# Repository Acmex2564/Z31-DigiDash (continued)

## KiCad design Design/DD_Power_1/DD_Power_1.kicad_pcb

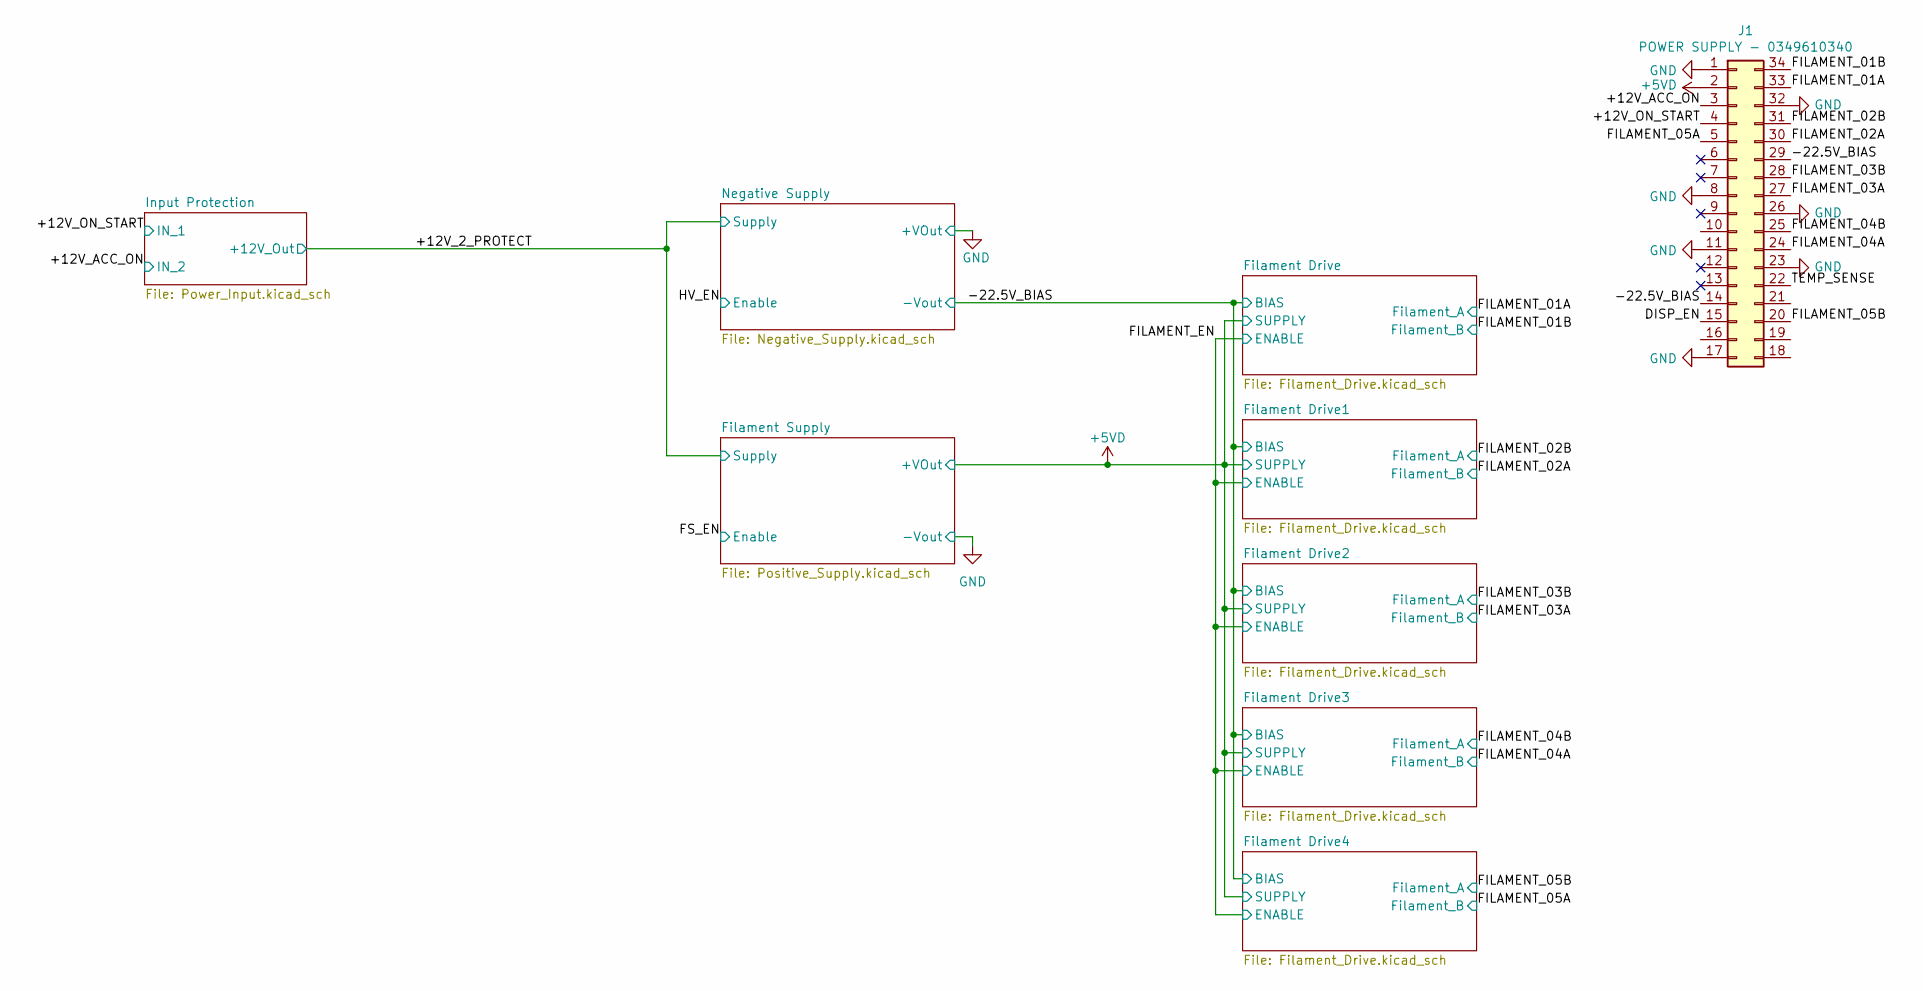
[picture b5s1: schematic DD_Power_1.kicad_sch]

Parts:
J1: POWER SUPPLY - 0349610340; 34961

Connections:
+5VD: J1.2; also elsewhere on the board
/+12V_ACC_ON: J1.3; also elsewhere on the board
/+12V_CONST: J1.21
/+12V_ON_START: J1.4; also elsewhere on the board
/-22.5V_BIAS: J1.14, J1.29; also elsewhere on the board
/DISP_EN: J1.15
/FILAMENT_01A: J1.33; also elsewhere on the board
/FILAMENT_01B: J1.34; also elsewhere on the board
/FILAMENT_02A: J1.30; also elsewhere on the board
/FILAMENT_02B: J1.31; also elsewhere on the board
/FILAMENT_03A: J1.27; also elsewhere on the board
/FILAMENT_03B: J1.28; also elsewhere on the board
/FILAMENT_04A: J1.24; also elsewhere on the board
/FILAMENT_04B: J1.25; also elsewhere on the board
/FILAMENT_05A: J1.5; also elsewhere on the board
/FILAMENT_05B: J1.20; also elsewhere on the board
/TEMP_SENSE: J1.22
GND: J1.1, J1.8, J1.11, J1.17, J1.23, J1.26, J1.32; also elsewhere on the board

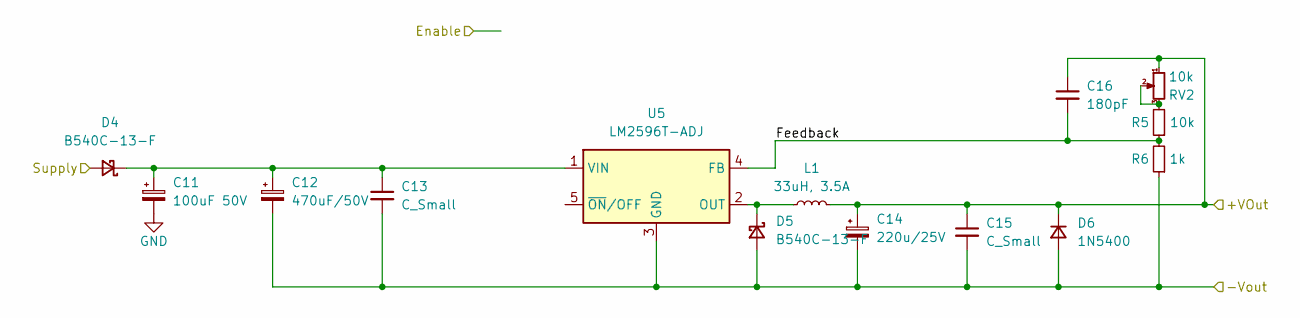
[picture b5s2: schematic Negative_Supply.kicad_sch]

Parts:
C11: 100uF 50V; CP_Radial_D8.0mm_P3.50mm
C12: 470uF/50V; CP_Radial_D12.5mm_P5.00mm
C13, C15: C_Small; C_0805_2012Metric_Pad1.18x1.45mm_HandSolder
C14: 220u/25V; CP_Radial_D6.3mm_P2.50mm
C16: 180pF; C_0805_2012Metric_Pad1.18x1.45mm_HandSolder
D4, D5: B540C-13-F; D_SMC
D6: 1N5400; D_SMC
L1: 33uH, 3.5A; L_Bourns_SRR1260
R5: 10k; R_0805_2012Metric_Pad1.20x1.40mm_HandSolder
R6: 1k; R_0805_2012Metric_Pad1.20x1.40mm_HandSolder
RV2: 10k; Potentiometer_Vishay_TS53YJ_Vertical
U5: LM2596T-ADJ; TO-220-5_P3.4x3.7mm_StaggerOdd_Lead3.8mm_Vertical

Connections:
/+12V_2_PROTECT: D4.2 (A); also elsewhere on the board
/-22.5V_BIAS: C12.2, C13.2, C14.2, C15.2, D5.2 (A), D6.2 (A), R6.1, U5.3 (GND); also elsewhere on the board
/Negative Supply/Feedback: C16.2, R5.1, R6.2, U5.4 (FB)
GND: C11.2, C14.1, C15.1, C16.1, D6.1 (K), L1.2, RV2.1; also elsewhere on the board
unnamed: C11.1, C12.1, C13.1, D4.1 (K), U5.1 (VIN)
unnamed: D5.1 (K), L1.1, U5.2 (OUT)
unnamed: R5.2, RV2.2, RV2.3

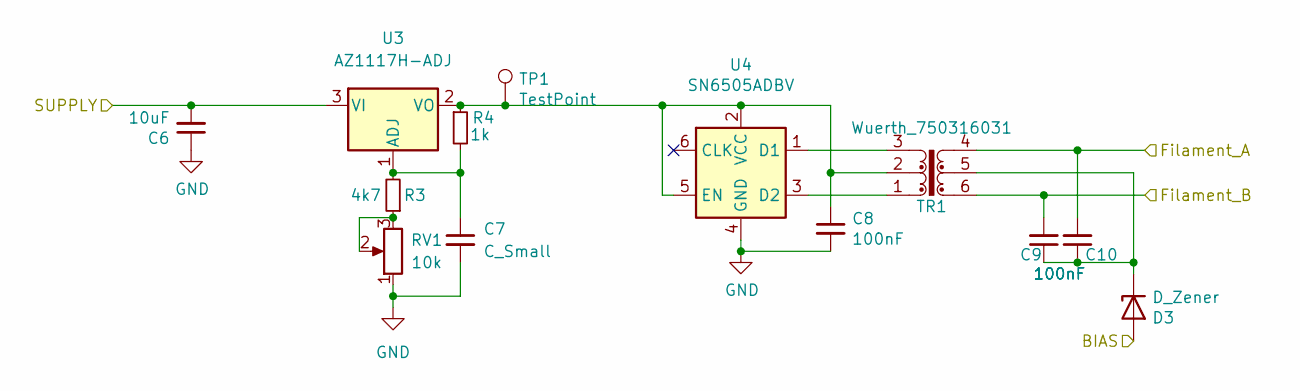
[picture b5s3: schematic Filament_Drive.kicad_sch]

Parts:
C6: 10uF; C_1206_3216Metric_Pad1.33x1.80mm_HandSolder
C7: C_Small; C_0805_2012Metric_Pad1.18x1.45mm_HandSolder
C8, C9, C10: 100nF; C_0805_2012Metric_Pad1.18x1.45mm_HandSolder
D3: D_Zener; D_SOD-123
R3: 4k7; R_0805_2012Metric_Pad1.20x1.40mm_HandSolder
R4: 1k; R_0805_2012Metric_Pad1.20x1.40mm_HandSolder
RV1: 10k; Potentiometer_Vishay_TS53YL_Vertical
TP1: TestPoint; TestPoint_2Pads_Pitch2.54mm_Drill0.8mm
TR1: Wuerth_750316031; Transformer_Wuerth_750315371
U3: AZ1117H-ADJ; SOT-223-3_TabPin2
U4: SN6505ADBV; SOT-23-6

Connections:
+5VD: C6.2, U3.3 (VI); also elsewhere on the board
/-22.5V_BIAS: D3.2 (A); also elsewhere on the board
/FILAMENT_01A: C10.2, TR1.4; also elsewhere on the board
/FILAMENT_01B: C9.2, TR1.6; also elsewhere on the board
GND: C6.1, C7.2, C8.2, RV1.1, U4.4 (GND); also elsewhere on the board
unnamed: C7.1, R3.2, R4.2, U3.1 (ADJ)
unnamed: C8.1, R4.1, TP1.1, TR1.2, U3.2 (VO), U4.2 (VCC), U4.5 (EN)
unnamed: C9.1, C10.1, D3.1 (K), TR1.5
unnamed: R3.1, RV1.2, RV1.3
unnamed: TR1.1, U4.3 (D2)
unnamed: TR1.3, U4.1 (D1)

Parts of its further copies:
C21, C26, C31, C36: 10uF; C_1206_3216Metric_Pad1.33x1.80mm_HandSolder
C22, C27, C32, C37: C_Small; C_0805_2012Metric_Pad1.18x1.45mm_HandSolder
C23, C24, C25, C28, C29, C30, C33, C34, C35, C38, C39, C40: 100nF; C_0805_2012Metric_Pad1.18x1.45mm_HandSolder
D8, D9, D10, D11: D_Zener; D_SOD-123
R7, R9, R11, R13: 4k7; R_0805_2012Metric_Pad1.20x1.40mm_HandSolder
R8, R10, R12, R14: 1k; R_0805_2012Metric_Pad1.20x1.40mm_HandSolder
RV3, RV4, RV5, RV6: 10k; Potentiometer_Vishay_TS53YL_Vertical
TP2, TP3, TP4, TP5: TestPoint; TestPoint_2Pads_Pitch2.54mm_Drill0.8mm
TR2, TR3, TR4, TR5: Wuerth_750316031; Transformer_Wuerth_750315371
U7, U9, U11, U13: AZ1117H-ADJ; SOT-223-3_TabPin2
U8, U10, U12, U14: SN6505ADBV; SOT-23-6

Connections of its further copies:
+5VD: C21.2, C26.2, C31.2, C36.2, U7.3 (VI), U9.3 (VI), U11.3 (VI), U13.3 (VI); also elsewhere on the board
/-22.5V_BIAS: D8.2 (A), D9.2 (A), D10.2 (A), D11.2 (A); also elsewhere on the board
/FILAMENT_02A: C24.2, TR2.6; also elsewhere on the board
/FILAMENT_02B: C25.2, TR2.4; also elsewhere on the board
/FILAMENT_03A: C29.2, TR3.6; also elsewhere on the board
/FILAMENT_03B: C30.2, TR3.4; also elsewhere on the board
/FILAMENT_04A: C34.2, TR4.6; also elsewhere on the board
/FILAMENT_04B: C35.2, TR4.4; also elsewhere on the board
/FILAMENT_05A: C39.2, TR5.6; also elsewhere on the board
/FILAMENT_05B: C40.2, TR5.4; also elsewhere on the board
GND: C21.1, C22.2, C23.2, C26.1, C27.2, C28.2, C31.1, C32.2, C33.2, C36.1, C37.2, C38.2, RV3.1, RV4.1, RV5.1, RV6.1, U8.4 (GND), U10.4 (GND), U12.4 (GND), U14.4 (GND); also elsewhere on the board
unnamed: C22.1, R7.2, R8.2, U7.1 (ADJ)
unnamed: C23.1, R8.1, TP2.1, TR2.2, U7.2 (VO), U8.2 (VCC), U8.5 (EN)
unnamed: C24.1, C25.1, D8.1 (K), TR2.5
unnamed: C27.1, R9.2, R10.2, U9.1 (ADJ)
unnamed: C28.1, R10.1, TP3.1, TR3.2, U9.2 (VO), U10.2 (VCC), U10.5 (EN)
unnamed: C29.1, C30.1, D9.1 (K), TR3.5
unnamed: C32.1, R11.2, R12.2, U11.1 (ADJ)
unnamed: C33.1, R12.1, TP4.1, TR4.2, U11.2 (VO), U12.2 (VCC), U12.5 (EN)
unnamed: C34.1, C35.1, D10.1 (K), TR4.5
unnamed: C37.1, R13.2, R14.2, U13.1 (ADJ)
unnamed: C38.1, R14.1, TP5.1, TR5.2, U13.2 (VO), U14.2 (VCC), U14.5 (EN)
unnamed: C39.1, C40.1, D11.1 (K), TR5.5
unnamed: R7.1, RV3.2, RV3.3
unnamed: R9.1, RV4.2, RV4.3
unnamed: R11.1, RV5.2, RV5.3
unnamed: R13.1, RV6.2, RV6.3
unnamed: TR2.1, U8.3 (D2)
unnamed: TR2.3, U8.1 (D1)
unnamed: TR3.1, U10.3 (D2)
unnamed: TR3.3, U10.1 (D1)
unnamed: TR4.1, U12.3 (D2)
unnamed: TR4.3, U12.1 (D1)
unnamed: TR5.1, U14.3 (D2)
unnamed: TR5.3, U14.1 (D1)

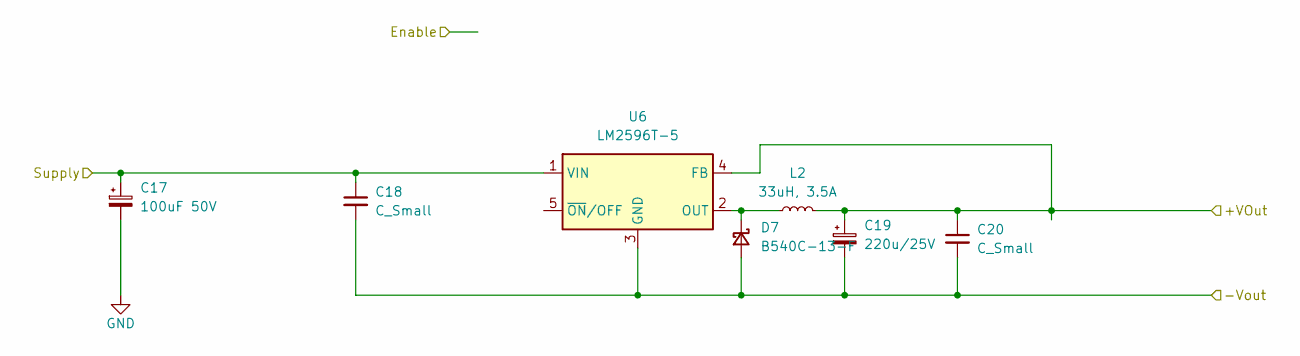
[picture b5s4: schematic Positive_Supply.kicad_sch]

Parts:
C17: 100uF 50V; CP_Radial_D8.0mm_P3.50mm
C18, C20: C_Small; C_0805_2012Metric_Pad1.18x1.45mm_HandSolder
C19: 220u/25V; CP_Radial_D6.3mm_P2.50mm
D7: B540C-13-F; D_SMC
L2: 33uH, 3.5A; L_Bourns_SRR1260
U6: LM2596T-5; TO-220-5_P3.4x3.7mm_StaggerOdd_Lead3.8mm_Vertical

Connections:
+5VD: C19.1, C20.1, L2.2, U6.4 (FB); also elsewhere on the board
/+12V_2_PROTECT: C17.1, C18.1, U6.1 (VIN); also elsewhere on the board
GND: C17.2, C18.2, C19.2, C20.2, D7.2 (A), U6.3 (GND); also elsewhere on the board
unnamed: D7.1 (K), L2.1, U6.2 (OUT)

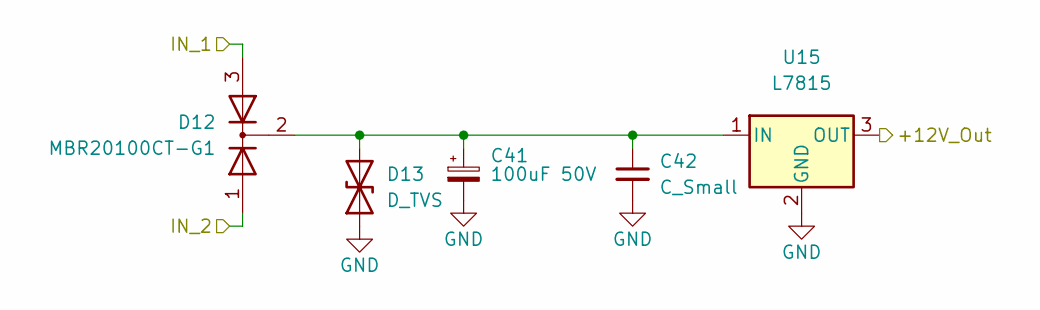
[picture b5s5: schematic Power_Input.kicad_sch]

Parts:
C41: 100uF 50V; CP_Radial_D8.0mm_P3.50mm
C42: C_Small
D12: MBR20100CT-G1; TO-220-3_Vertical
D13: D_TVS; D_SMC
U15: L7815; TO-220-3_Vertical

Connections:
/+12V_2_PROTECT: U15.3 (OUT); also elsewhere on the board
/+12V_ACC_ON: D12.1 (A); also elsewhere on the board
/+12V_ON_START: D12.3 (A); also elsewhere on the board
GND: C41.2, C42.2, D13.1 (A1), U15.2 (GND); also elsewhere on the board
unnamed: C41.1, C42.1, D12.2 (K), D13.2 (A2), U15.1 (IN)

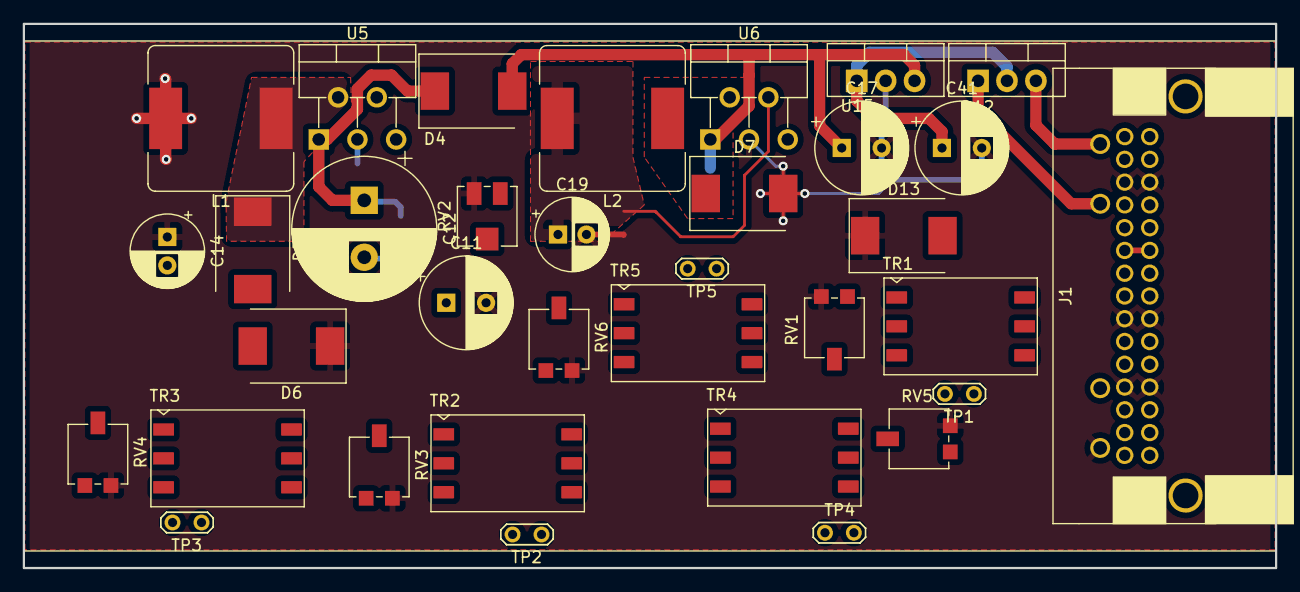
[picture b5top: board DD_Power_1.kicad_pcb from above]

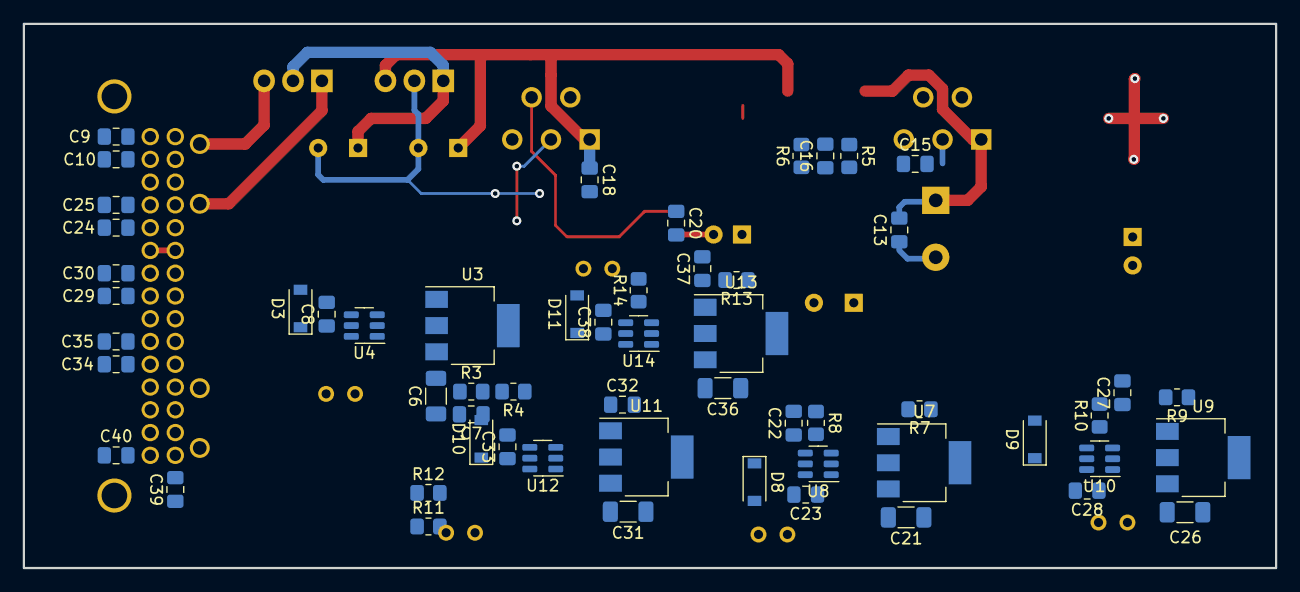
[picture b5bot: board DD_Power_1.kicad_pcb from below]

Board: 4 copper layers, 110.0 x 47.8 mm, 91 parts (57 on the bottom side), 52 nets.

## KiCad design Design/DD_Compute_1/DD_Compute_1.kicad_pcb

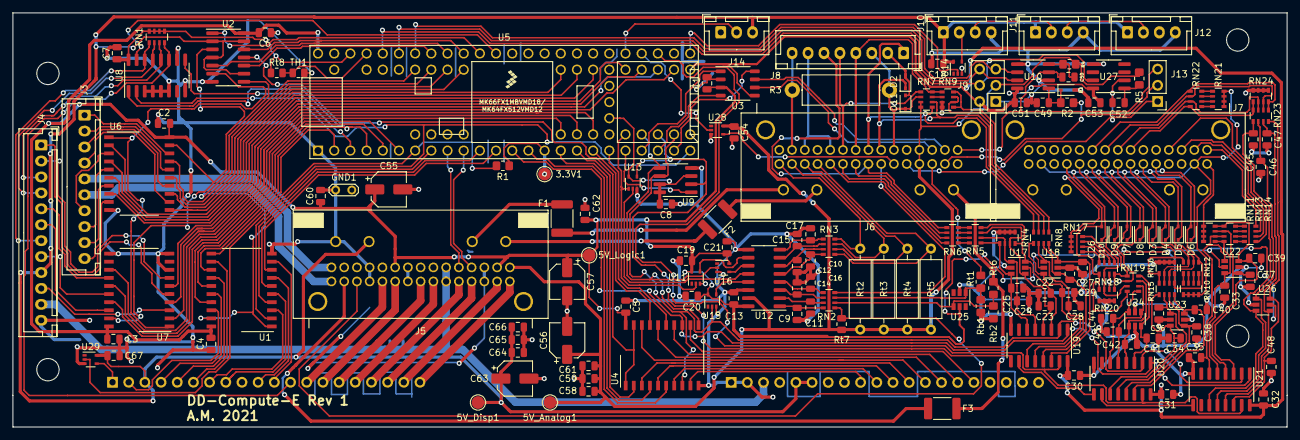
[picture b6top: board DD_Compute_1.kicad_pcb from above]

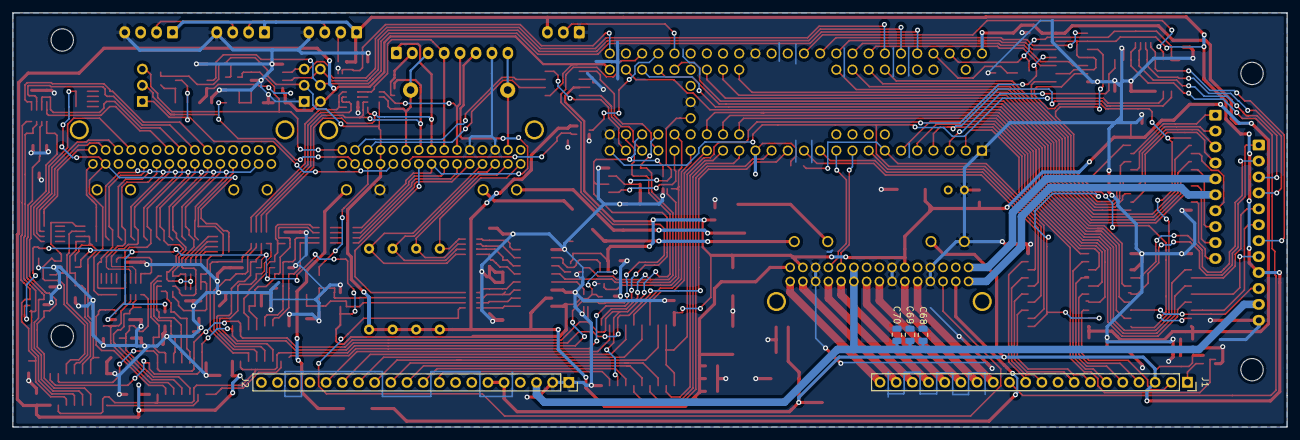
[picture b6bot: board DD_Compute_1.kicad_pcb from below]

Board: 2 copper layers, 200.0 x 65.0 mm, 172 parts (5 on the bottom side), 226 nets.

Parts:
3.3V1, 5V_Analog1, 5V_Disp1, 5V_Logic1: TestPoint; TestPoint_Pad_D2.0mm
C1, C2, C3, C4, C5, C6, C7, C8, C10, C59, C65, C69: 100nF; C_0805_2012Metric
C9, C11, C12, C14, C15, C17, C18, C19, C20, C21, C22, C23, C24, C25, C26, C27, C28, C29, C30, C31, C32, C33, C34, C35, C36, C37, C38, C39, C40, C41, C42, C43, C44, C45, C46, C47, C48, C51, C53, C54, C67: 100n; C_0805_2012Metric
C13, C58, C60, C62, C64, C68: 1uF; C_0805_2012Metric
C16, C49, C50, C52: 10n; C_0805_2012Metric
C55, C56, C57, C63: 47uF; CP_Elec_5x5.3
C61, C66, C70: 10nF; C_0805_2012Metric
D1, D2, D3, D4, D5, D6, D7, D8, D9, D10, D11: 1N4148WS; D_SOD-323
F1, F2, F3: Polyfuse_Small; Fuse_1812_4532Metric_Pad1.30x3.40mm_HandSolder
GND1: TestPoint; TestPoint_2Pads_Pitch2.54mm_Drill0.8mm
J1: DISP. BOARD CONN 1 (1-20); PinSocket_1x20_P2.54mm_Vertical
J2: DISP. BOARD CONN 2 (21-40); PinSocket_1x20_P2.54mm_Vertical
J3: TRIP BOARD CONN 1 (1-10); JST_XH_B10B-XH-A_1x10_P2.50mm_Vertical
J4: TRIP BOARD CONN 2 (11-22); JST_XH_B12B-XH-A_1x12_P2.50mm_Vertical
J5: POWER SUPPLY - 0349580340; 34958
J6: CAR INTERFACE - 0349580340 - SIG; 34958
J7: CAR INTERFACE - 0349580341; 34958
J8: DISP_BOARD_CONN_3; JST_XH_B8B-XH-A_1x08_P2.50mm_Vertical
J9: ISOLATED OUPTUTS & POWER; PinHeader_2x03_P2.54mm_Vertical
J10, J11, J12: Conn_01x03; JST_XH_B4B-XH-A_1x04_P2.50mm_Vertical
J13: ISOLATED INPUTS; PinHeader_1x03_P2.54mm_Vertical
J14: ODOMETER MODULE; JST_XH_B3B-XH-A_1x03_P2.50mm_Vertical
R1: 47k; R_0805_2012Metric_Pad1.20x1.40mm_HandSolder
R2: 2.2k; R_0805_2012Metric_Pad1.20x1.40mm_HandSolder
R3: 47; R_Axial_DIN0414_L11.9mm_D4.5mm_P15.24mm_Horizontal
R4, R5: 1k; R_0805_2012Metric_Pad1.20x1.40mm_HandSolder
RN1, RN2, RN3, RN4, RN5, RN6, RN7, RN8, RN9, RN10, RN11, RN12, RN13, RN14, RN15, RN16, RN17, RN18, RN19, RN20, RN21, RN22, RN23, RN24: 4.7k; R_Array_Convex_4x0603
Rb1, Rb2: 75k 1%; R_0805_2012Metric_Pad1.20x1.40mm_HandSolder
Rt1, Rt6: 35.7k 1%; R_0805_2012Metric_Pad1.20x1.40mm_HandSolder
Rt2, Rt3, Rt4, Rt5: R; R_Axial_DIN0309_L9.0mm_D3.2mm_P12.70mm_Horizontal
Rt7, Rt8: 47k; R_0805_2012Metric
TH1: NTCG204AH473JT1; R_0805_2012Metric
U1, U4, U6, U7: 74HCT244D,653; SO-20_12.8x7.5mm_P1.27mm
U2: 74HCT00D,653; SO-14_3.9x8.65mm_P1.27mm
U3: TLE6250GV33; SSOP-8_3.9x5.05mm_P1.27mm
U5: Teensy3.6; Teensy35_36_centerpins
U8, U19, U20, U21: 74HC165D-Q100,118; SOIC-16_3.9x9.9mm_P1.27mm
U9: 25LC020AT-E/SN; SOIC-8_3.9x4.9mm_P1.27mm
U10, U27: VO0631T; SOIC-8_3.9x4.9mm_P1.27mm
U11, U14, U15, U16, U28, U29: SN74LV1T34DCK; SOT-353_SC-70-5
U12: MCP3008; SOIC-16_3.9x9.9mm_P1.27mm
U13: SN74AHC1G125DCK3; SOT-353_SC-70-5
U17, U18, U22, U23, U24, U25, U26: SRV05-4; SOT-23-6

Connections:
12V_Sense: RN2.2, Rb2.1, Rt6.2, U25.4
+3V3: 3.3V1.1, C7.1, C8.2, C30.1, C31.1, C32.1, C51.2, C53.2, J9.2, R1.2, RN1.5, RN1.6, RN1.7, RN1.8, Rt8.1, U3.5, U5.15, U5.26, U5.51, U5.75, U8.16, U9.3, U9.7, U9.8, U10.8, U13.5, U19.16, U20.16, U21.16, U27.8
+5V: 5V_Logic1.1, C1.1, C2.2, C3.1, C4.2, C5.2, C6.2, C13.1, C19.1, C20.1, C21.1, C55.1, C57.1, C60.1, C62.1, J5.10, J5.18, U1.20, U2.14, U3.3, U4.20, U5.53, U6.20, U7.20, U11.5, U12.16, U15.5, U16.5, U17.5, U18.5, U22.5, U23.5, U24.5, U25.5, U26.5
+5VA: 5V_Analog1.1, C54.1, C56.1, C58.1, C59.1, C61.1, J5.19, J6.8, J6.23, J9.3, R4.2, R5.2, RN7.3, RN7.4, Rt2.1, Rt3.1, Rt4.1, Rt5.1, Rt7.1, U12.15, U28.5
+5VD: 5V_Disp1.1, C18.1, C63.1, C64.1, C65.1, C66.1, C67.1, J1.3, J2.5, J2.6, J4.9, J5.2, J10.1, J11.1, J12.1, J14.3, U2.2, U2.4, U2.9, U2.13, U14.5, U29.5
+12V_ACC_ON: F1.2, J6.4
+12V_CONST: F3.1, J6.1, Rt6.1
+12V_ON_START: F2.2, J6.3
+12V_ON_START_B: J6.33, J8.8, R3.1
+12V_Security: J6.29, J8.5, RN7.1
/Illum_Data_Loop1: J10.3, J11.2
/Illum_Data_Loop2: J11.3, J12.2
/Illum_Data_Out: J10.2, U14.4
/Secondary_Warning_Input/ASCD_CruiseB: C23.2, RN4.7, RN5.7, U17.4, U19.4
/Secondary_Warning_Input/ASCD_OnB: C22.2, RN4.8, RN5.8, U17.6, U19.3
/Secondary_Warning_Input/ASCD_Set_Disp_1B: C24.2, RN4.6, RN5.6, U17.1, U19.5
/Secondary_Warning_Input/ASCD_Set_Disp_2B: C25.2, RN4.5, RN5.5, U17.3, U19.6
/Secondary_Warning_Input/Belt: C34.2, RN15.1, U20.11, U23.3
/Secondary_Warning_Input/Brake_1: C38.2, RN15.3, U20.13, U23.4
/Secondary_Warning_Input/Brake_2: C40.2, RN15.4, U20.14, U23.6
/Secondary_Warning_Input/Coolant: C41.2, RN19.8, U20.3, U24.3
/Secondary_Warning_Input/Door: C44.2, RN19.5, U20.6, U24.6
/Secondary_Warning_Input/Extra_HighB: C39.2, RN11.4, RN13.5, U21.3, U22.3
/Secondary_Warning_Input/Extra_Low_1B: C45.2, RN23.1, U21.11, U26.3
/Secondary_Warning_Input/Extra_Low_2B: C46.2, RN23.2, U21.12, U26.1
/Secondary_Warning_Input/Extra_Low_3B: C47.2, RN23.3, U21.13, U26.4
/Secondary_Warning_Input/Extra_Low_4B: C48.2, RN23.4, U21.14, U26.6
/Secondary_Warning_Input/Headlamp: C42.2, RN19.7, U20.4, U24.1
/Secondary_Warning_Input/Left_Turn: C35.2, RN11.2, RN13.7, U21.6, U22.4
/Secondary_Warning_Input/Main_Beam: C33.2, RN11.1, RN13.8, U21.5, U22.6
/Secondary_Warning_Input/Right_Turn: C37.2, RN11.3, RN13.6, U21.4, U22.1
/Secondary_Warning_Input/Sensor: C36.2, RN15.2, U20.12, U23.1
/Secondary_Warning_Input/Taillamp: C43.2, RN19.6, U20.5, U24.4
/Secondary_Warning_Input/Warn_ChargeB: C27.2, RN8.7, U18.1, U19.13
/Secondary_Warning_Input/Warn_FuelB: C28.2, RN8.6, U18.4, U19.12
/Secondary_Warning_Input/Warn_Oil_PressB: C29.2, RN8.5, U18.6, U19.11
/Secondary_Warning_Input/Warn_SecurityB: C26.2, RN8.8, U18.3, U19.14
/Warning_Extra_1: J7.26, RN22.8, RN23.8, RN24.1
/Warning_Extra_2: J7.27, RN22.7, RN23.7, RN24.2
/Warning_Extra_3: J7.28, RN22.6, RN23.6, RN24.3
/Warning_Extra_4: J7.29, RN22.5, RN23.5, RN24.4
ANALOG_EN: J5.16, U5.10
ASCD_Cruise: J6.13, RN6.2
ASCD_On: J6.12, J8.6, RN6.1
ASCD_Set_Disp_1: J6.14, RN6.3
ASCD_Set_Disp_2: J6.15, RN6.4
Bias_Grid_Anode: C68.1, C69.1, C70.1, J2.3, J4.11, J5.14, J5.29
Blanking_Control: R1.1, U5.7, U29.2
CAN_INH: U3.8, U5.23
CAN_RX: U3.4, U5.22
CAN_TX: U3.1, U5.21
CTL_IC31: U5.76, U7.2
Clock_1_(Time): J6.21, U3.7
Clock_2_(Time): J6.22, U3.6
Coil_Negative_(Tach): J6.6, J13.2, R2.2
DISP_EN: J5.15, U5.9
Disp_CTL_IC31: J4.6, U7.18
Disp_Mode_IC30: J4.10, U7.3
Disp_Reset_IC30: J4.1, U7.5
Disp_Reset_IC31: J4.8, U7.16
Disp_S0_IC30: J3.7, U6.3
Disp_S0_IC31: J3.1, U6.18
Disp_S1_IC30: J3.8, U6.5
Disp_S1_IC31: J3.2, U6.16
Disp_S2_IC30: J3.9, U6.7
Disp_S2_IC31: J3.3, U6.14
Disp_S3_IC30: J3.10, U6.9
Disp_S3_IC31: J3.4, U6.12
Disp_~WR~_IC30: J4.2, U7.7
Disp_~WR~_IC31: J4.5, U7.14
Display_Blank_Input: J1.1, U29.4
Display_CS_DrvRA4: J2.14, U4.16
Display_CS_DrvRA5: J2.15, U4.14
Display_CS_DrvRA7: J2.11, U4.5
Display_CS_DrvRA10: J2.13, U4.18
Display_CS_DrvRA12: J2.12, U4.3
Display_CS_Fuel_Lvl: J1.8, U1.5
Display_CS_Fuel_Qty: J1.4, U1.16
Display_CS_Oil: J1.5, U1.14
Display_CS_Temp: J1.6, U1.12
Display_CS_Volts: J1.7, U1.3
Display_LH_Main: J2.10, U4.7
Display_LH_Satellite: J1.10, U1.7
Display_SCK_Main: J2.16, U4.12
Display_SCK_Satellite: J1.2, U1.18
Display_SI_Main: J2.9, U4.9
Display_SI_Satellite: J1.11, U1.9
Extra_High_Input: J7.20, RN14.4
Filament_Fuel_A: J1.19, J5.33
Filament_Fuel_B: J1.20, J5.34
Filament_Speed_A: J1.17, J5.30
Filament_Speed_B: J1.18, J5.31
Filament_Sub_A: J1.13, J5.24
Filament_Sub_B: J1.14, J5.25
Filament_Tach_A: J1.15, J5.27
Filament_Tach_B: J1.16, J5.28
Filament_Trip_A: J3.5, J5.5
Filament_Trip_B: J3.6, J5.20
Fuel_Gauge_Main: J6.16, RN3.1, Rt5.2
Fuel_Gauge_Sub: J6.17, RN3.2, Rt4.2
Fuel_Injection_Pulse: C50.1, J6.20, J13.3, U10.3
Fuel_Injection_Pulse_Protect: J9.5, U5.47, U10.6
GND: C1.2, C2.1, C3.2, C4.1, C5.1, C6.1, C7.2, C8.1, C9.1, C10.1, C11.1, C12.1, C13.2, C14.1, C15.1, C16.1, C17.1, C18.2, C19.2, C20.2, C21.2, C22.1, C23.1, C24.1, C25.1, C26.1, C27.1, C28.1, C29.1, C30.2, C31.2, C32.2, C33.1, C34.1, C35.1, C36.1, C37.1, C38.1, C39.1, C40.1, C41.1, C42.1, C43.1, C44.1, C45.1, C46.1, C47.1, C48.1, C49.2, C51.1, C53.1, C54.2, C55.2, C56.2, C57.2, C58.2, C59.2, C60.2, C61.2, C62.2, C63.2, C64.2, C65.2, C66.2, C67.2, C68.2, C69.2, C70.2, D1.2, GND1.1, J2.1, J2.2, J4.12, J5.1, J5.8, J5.11, J5.17, J5.23, J5.26, J5.32, J6.2, J6.30, J6.32, J8.7, J9.1, J10.4, J11.4, J12.4, J14.1, RN4.1, RN4.2, RN4.3, RN4.4, RN9.3, RN9.4, RN16.5, RN16.6, RN16.7, RN16.8, RN20.5, RN20.6, RN20.7, RN20.8, RN24.5, RN24.6, RN24.7, RN24.8, Rb1.2, Rb2.2, TH1.2, U1.10, U2.7, U3.2, U4.10, U5.1, U5.27, U5.39, U5.74, U6.10, U7.8, U7.10, U7.11, U8.3, U8.4, U8.5, U8.6, U8.8, U8.10, U9.4, U10.2, U10.5, U11.3, U12.9, U12.14, U13.3, U14.3, U15.3, U16.3, U17.2, U18.2, U19.8, U20.8, U21.8, U22.2, U23.2, U24.2, U25.2, U26.2, U27.5, U28.3, U29.3
IC30_OE: U2.1, U5.43
IC31_OE: U2.5, U5.45
INT_TEMP_SENSE: Rt8.2, TH1.1, U5.50
Illum_Data: U5.30, U14.2
Illum_Sense: RN2.3, Rb1.1, Rt1.2, U25.1
Illumination_2: J6.7, Rt1.1
Indicator_Pilot_Common: J7.5, RN11.5, RN11.6, RN11.7, RN11.8
Indicator_Pilot_Left: J7.22, RN14.2
Indicator_Pilot_Main: J7.23, RN14.1
Indicator_Pilot_Right: J7.21, RN14.3
Main_Enable: U2.12, U5.44
Manifold_Pressure: J6.11, RN2.4
Mode_IC30: U5.67, U7.17
unnamed: C9.2, RN2.8, U12.1
unnamed: C10.2, RN3.8, U12.5
unnamed: C11.2, RN2.7, U12.2
unnamed: C12.2, RN3.7, U12.6
unnamed: C14.2, RN2.6, U12.3
unnamed: C15.2, RN3.6, U12.7
unnamed: C16.2, RN2.5, U12.4
unnamed: C17.2, RN3.5, U12.8
unnamed: C49.1, D1.1, R2.1, U10.1
unnamed: C50.2, R4.1, U10.4
unnamed: C52.2, R5.1, U27.1
unnamed: D2.2, D11.2, J8.2
unnamed: F1.1, J5.3
unnamed: F2.1, J5.4
unnamed: F3.2, J5.21
unnamed: RN5.1, RN6.8
unnamed: RN5.2, RN6.7
unnamed: RN5.3, RN6.6
unnamed: RN5.4, RN6.5
unnamed: RN7.7, RN9.2
unnamed: RN8.1, RN9.5, RN9.8
unnamed: RN8.2, RN9.6, RN9.7
unnamed: RN10.5, RN12.4
unnamed: RN10.6, RN12.3
unnamed: RN10.7, RN12.2
unnamed: RN10.8, RN12.1
unnamed: RN13.1, RN14.8
unnamed: RN13.2, RN14.7
unnamed: RN13.3, RN14.6
unnamed: RN13.4, RN14.5
unnamed: RN17.5, RN18.4
unnamed: RN17.6, RN18.3
unnamed: RN17.7, RN18.2
unnamed: RN17.8, RN18.1
unnamed: RN21.5, RN22.4
unnamed: RN21.6, RN22.3
unnamed: RN21.7, RN22.2
unnamed: RN21.8, RN22.1
unnamed: U1.1, U1.19, U2.8
unnamed: U2.3, U6.19, U7.19
unnamed: U2.6, U6.1, U7.1
unnamed: U2.11, U4.1, U4.19
unnamed: U11.4, U12.10
unnamed: U12.11, U16.4
unnamed: U12.12, U13.2
unnamed: U12.13, U15.4
unnamed: U19.10, U20.9
unnamed: U20.10, U21.9
ODOMETER_SIGNAL: J14.2, U5.34
Oil_Pressure: J6.18, RN3.3, Rt3.2
PS_TEMP_SENSE: J5.22, RN2.1, Rt7.2
Reset_IC30: U5.68, U7.15
Reset_IC31: U5.77, U7.4
S0_IC30: U5.86, U6.17
S0_IC31: U5.82, U6.2
S1_IC30: U5.85, U6.15
S1_IC31: U5.81, U6.4
S2_IC30: U5.84, U6.13
S2_IC31: U5.80, U6.6
S3_IC30: U5.83, U6.11
S3_IC31: U5.79, U6.8
SPI1_CS0: U1.15, U5.5
SPI1_CS1: U1.17, U5.6
SPI1_CS2: U1.8, U5.12
SPI1_CS3: U1.6, U5.11
SPI1_CS4: U1.4, U5.8
SPI1_CS5: U5.42, U8.15
SPI1_LH: U1.13, U5.4, U8.1
SPI1_MISO: U5.3, U8.9
SPI1_MOSI: U1.11, U5.2
SPI1_SCK: U1.2, U5.24, U8.2
SPI2_CS0: U4.2, U5.17
SPI2_CS1: U4.4, U5.16
SPI2_CS2: U4.6, U5.14
SPI2_CS3: U4.15, U5.19
SPI2_CS4: U4.17, U5.18
SPI2_CS5: U5.20, U9.1
SPI2_CS6: U5.70, U11.2, U13.1
SPI2_CS7: U5.32, U19.15, U20.15, U21.15
SPI2_LH: U4.13, U5.13, U19.1, U20.1, U21.1
SPI2_MISO: U5.72, U9.2, U13.4, U19.9
SPI2_MOSI: U4.11, U5.71, U9.5, U16.2
SPI2_SCK: U4.8, U5.73, U9.6, U15.2, U19.2, U20.2, U21.2
SW_Indicated_Spd: J1.12, RN1.4, U8.11
SW_MPH-MPG: J4.7, RN1.1, U8.14
SW_Trip_A: J4.4, RN1.2, U8.13
SW_Trip_B: J4.3, RN1.3, U8.12
Satellite_Enable: U2.10, U5.46
Speed_Out: U5.33, U28.2
Speed_Sensor_In: C52.1, J6.9, J13.1, U27.2
Speed_Sensor_Protect: J9.4, U5.49, U27.7
Speed_Signal_Out: J6.10, U28.4
Tach_Protect: J9.6, U5.48, U10.7
Warning-12V-Supply: J7.6, RN10.1, RN10.2, RN10.3, RN10.4, RN17.1, RN17.2, RN17.3, RN17.4, RN21.1, RN21.2, RN21.3, RN21.4
Warning_Belt: D4.2, J7.11, RN12.7, RN15.7, RN16.2
Warning_Brake: D5.2, J7.10, RN12.6, RN15.6, RN16.3
Warning_Brake_2: D6.2, J7.9, RN12.5, RN15.5, RN16.4
Warning_Bulb_Check: D3.1, D4.1, D5.1, D6.1, D7.1, D8.1, D9.1, D10.1, J7.18
Warning_Charge: D11.1, J6.25, J8.3, R3.2, RN7.2
Warning_Coolant: D7.2, J7.14, RN18.8, RN19.1, RN20.1
Warning_Door: D10.2, J7.16, RN18.5, RN19.4, RN20.4
Warning_Fuel_Level: D2.1, J6.26, RN7.6, RN8.3
Warning_Headlamp: D8.2, J7.13, RN18.7, RN19.2, RN20.2
Warning_Oil_Pressure: J6.27, J8.1, RN7.5, RN8.4
Warning_Security: J6.28, J8.4, RN7.8, RN9.1
Warning_Sensor: D3.2, J7.12, RN12.8, RN15.8, RN16.1
Warning_Taillamp: D9.2, J7.15, RN18.6, RN19.3, RN20.3
Water_Temperature: J6.19, RN3.4, Rt2.2
~WR~_IC30: U5.69, U7.13
~WR~_IC31: U5.78, U7.6

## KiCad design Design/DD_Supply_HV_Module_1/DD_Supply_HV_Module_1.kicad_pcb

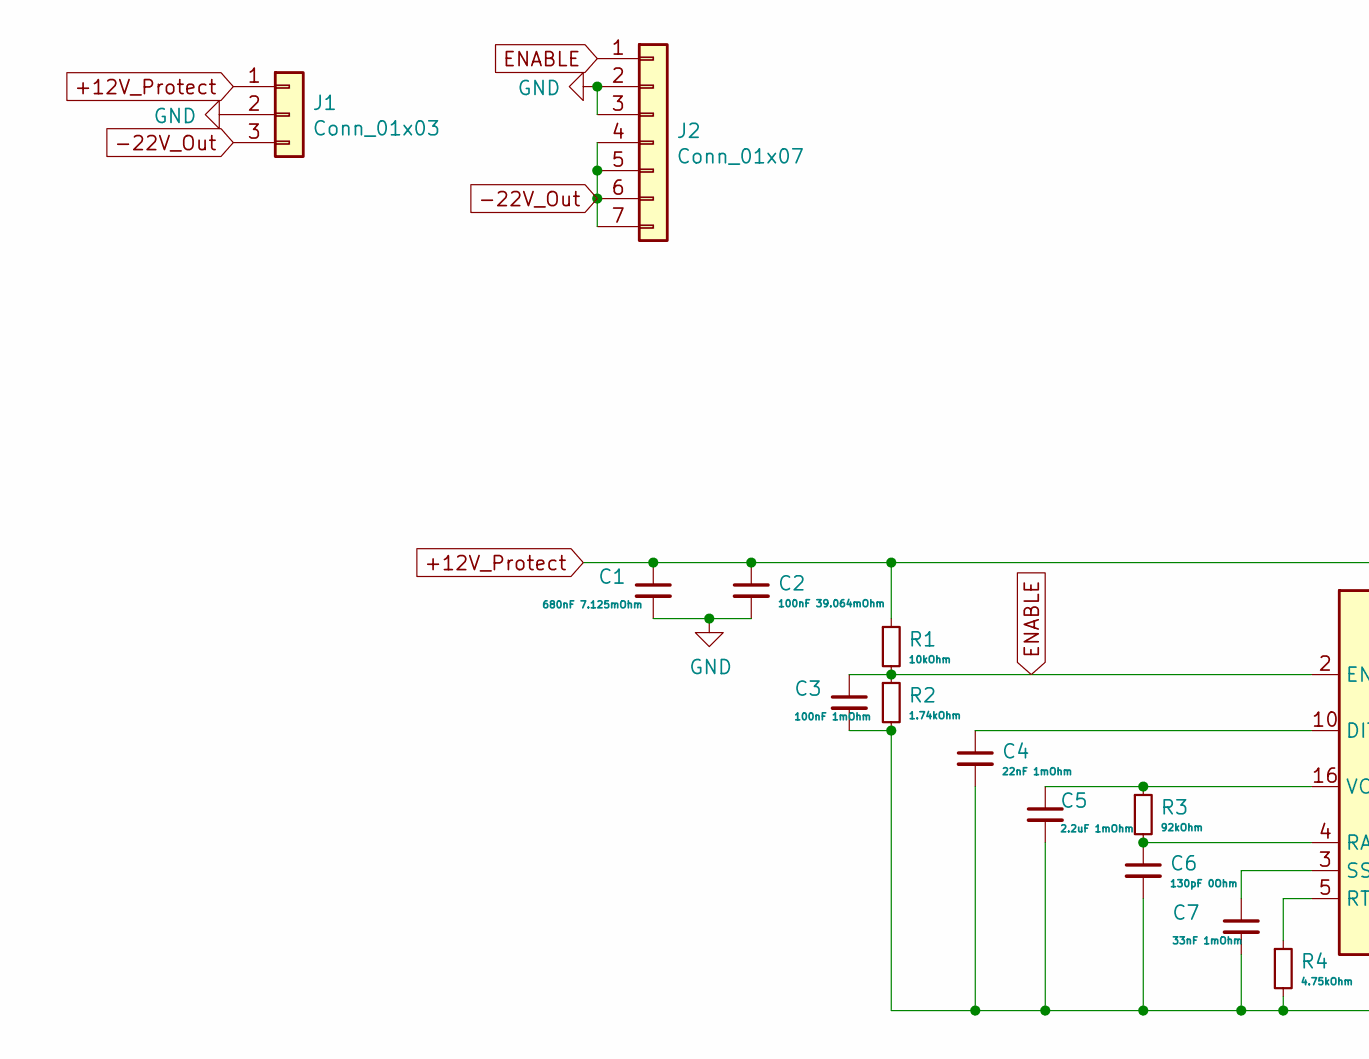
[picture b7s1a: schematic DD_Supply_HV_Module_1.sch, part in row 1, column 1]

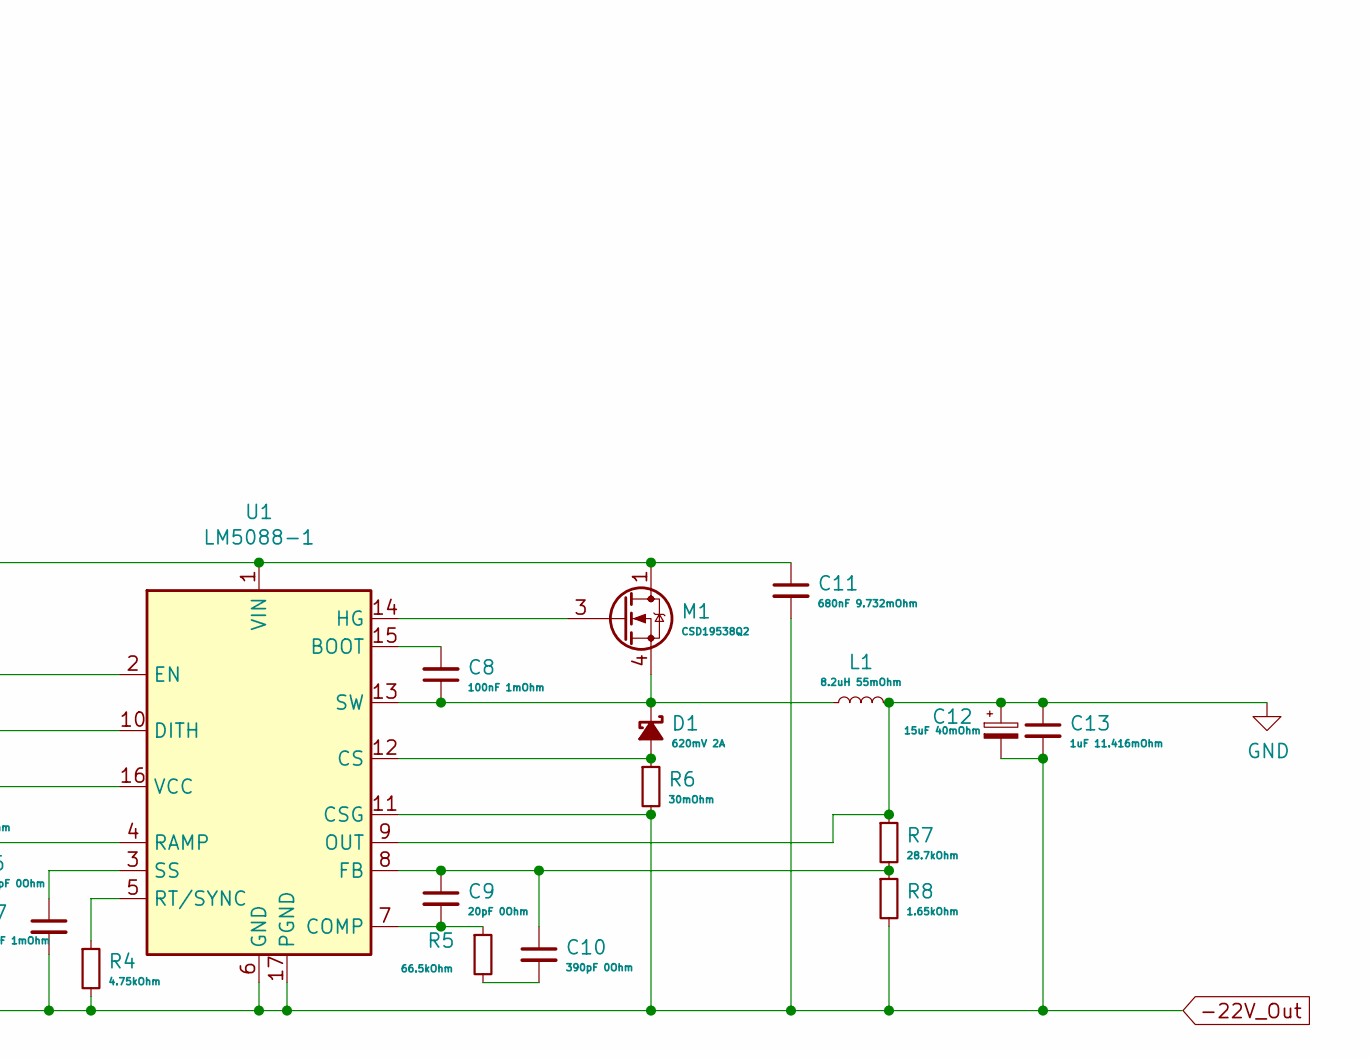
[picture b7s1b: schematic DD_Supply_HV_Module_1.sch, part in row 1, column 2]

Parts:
C1: 680nF 7.125mOhm; C_0805_2012Metric_Pad1.18x1.45mm_HandSolder
C2: 100nF 39.064mOhm; C_0805_2012Metric_Pad1.18x1.45mm_HandSolder
C3, C8: 100nF 1mOhm; C_0805_2012Metric_Pad1.18x1.45mm_HandSolder
C4: 22nF 1mOhm; C_0805_2012Metric_Pad1.18x1.45mm_HandSolder
C5: 2.2uF 1mOhm; C_0805_2012Metric_Pad1.18x1.45mm_HandSolder
C6: 130pF 0Ohm; C_0805_2012Metric_Pad1.18x1.45mm_HandSolder
C7: 33nF 1mOhm; C_0805_2012Metric_Pad1.18x1.45mm_HandSolder
C9: 20pF 0Ohm; C_0805_2012Metric_Pad1.18x1.45mm_HandSolder
C10: 390pF 0Ohm; C_0805_2012Metric_Pad1.18x1.45mm_HandSolder
C11: 680nF 9.732mOhm; C_0805_2012Metric_Pad1.18x1.45mm_HandSolder
C12: 15uF 40mOhm; CP_Elec_8x11.9
C13: 1uF 11.416mOhm; C_0805_2012Metric_Pad1.18x1.45mm_HandSolder
D1: 620mV 2A; SMP_DO-220AA
J1: Conn_01x03; PinHeader_1x03_P2.54mm_Vertical
J2: Conn_01x07; PinHeader_1x07_P2.54mm_Vertical
L1: 8.2uH 55mOhm; L_Bourns_SRN6045TA
M1: CSD19538Q2; Texas_DQK
R1: 10kOhm; R_0805_2012Metric_Pad1.20x1.40mm_HandSolder
R2: 1.74kOhm; R_0805_2012Metric_Pad1.20x1.40mm_HandSolder
R3: 92kOhm; R_0805_2012Metric_Pad1.20x1.40mm_HandSolder
R4: 4.75kOhm; R_0805_2012Metric_Pad1.20x1.40mm_HandSolder
R5: 66.5kOhm; R_0805_2012Metric_Pad1.20x1.40mm_HandSolder
R6: 30mOhm; R_1206_3216Metric_Pad1.30x1.75mm_HandSolder
R7: 28.7kOhm; R_0805_2012Metric_Pad1.20x1.40mm_HandSolder
R8: 1.65kOhm; R_0805_2012Metric_Pad1.20x1.40mm_HandSolder
U1: LM5088-1; HTSSOP-16-1EP_4.4x5mm_P0.65mm_EP3.4x5mm_Mask3x3mm_ThermalVi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

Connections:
+12V_Protect: C1.1, C2.1, C11.1, J1.1, M1.1 (D), M1.2 (D), M1.5 (D), M1.6 (D), M1.8 (D), R1.1, U1.1 (VIN)
-22V_Out: C3.2, C4.2, C5.2, C6.2, C7.2, C11.2, C12.2, C13.2, J1.3, J2.4, J2.5, J2.6, J2.7, R2.2, R4.2, R6.2, R8.2, U1.6 (GND), U1.11 (CSG), U1.17 (PGND)
ENABLE: C3.1, J2.1, R1.2, R2.1, U1.2 (EN)
GND: C1.2, C2.2, C12.1, C13.1, J1.2, J2.2, J2.3, L1.2, R7.1, U1.9 (OUT)
unnamed: C4.1, U1.10 (DITH)
unnamed: C5.1, R3.1, U1.16 (VCC)
unnamed: C6.1, R3.2, U1.4 (RAMP)
unnamed: C7.1, U1.3 (SS)
unnamed: C8.1, D1.1 (K), L1.1, M1.4 (S), M1.7 (S), U1.13 (SW)
unnamed: C8.2, U1.15 (BOOT)
unnamed: C9.2, R5.1, U1.7 (COMP)
unnamed: C9.1, C10.1, R7.2, R8.1, U1.8 (FB)
unnamed: C10.2, R5.2
unnamed: D1.2 (A), R6.1, U1.12 (CS)
unnamed: M1.3 (G), U1.14 (HG)
unnamed: R4.1, U1.5 (RT/SYNC)

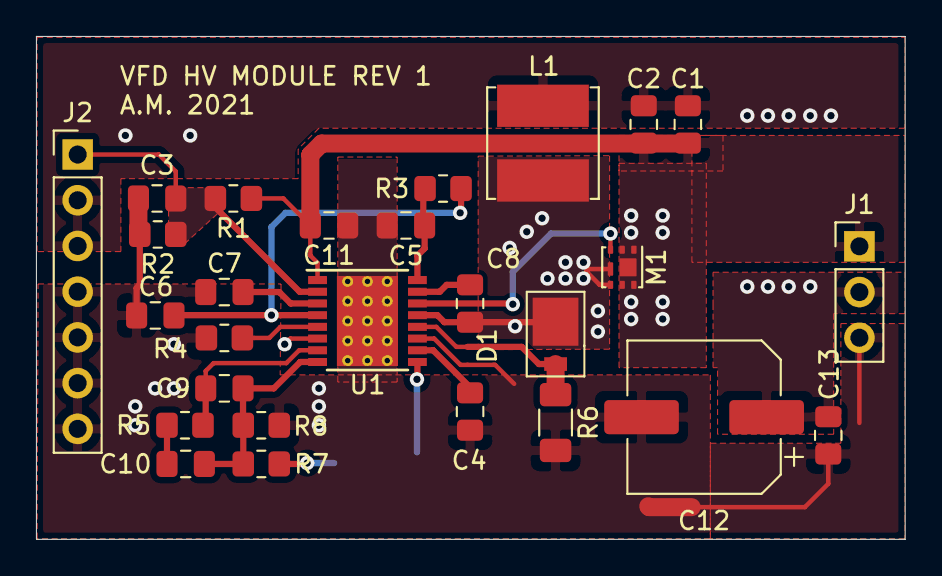
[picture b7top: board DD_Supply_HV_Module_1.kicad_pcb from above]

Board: 2 copper layers, 48.3 x 27.9 mm, 27 parts (0 on the bottom side), 16 nets.
